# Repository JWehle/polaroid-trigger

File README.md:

# polaroid-trigger
Automated trigger board for a polaroid SX-70 type camera.

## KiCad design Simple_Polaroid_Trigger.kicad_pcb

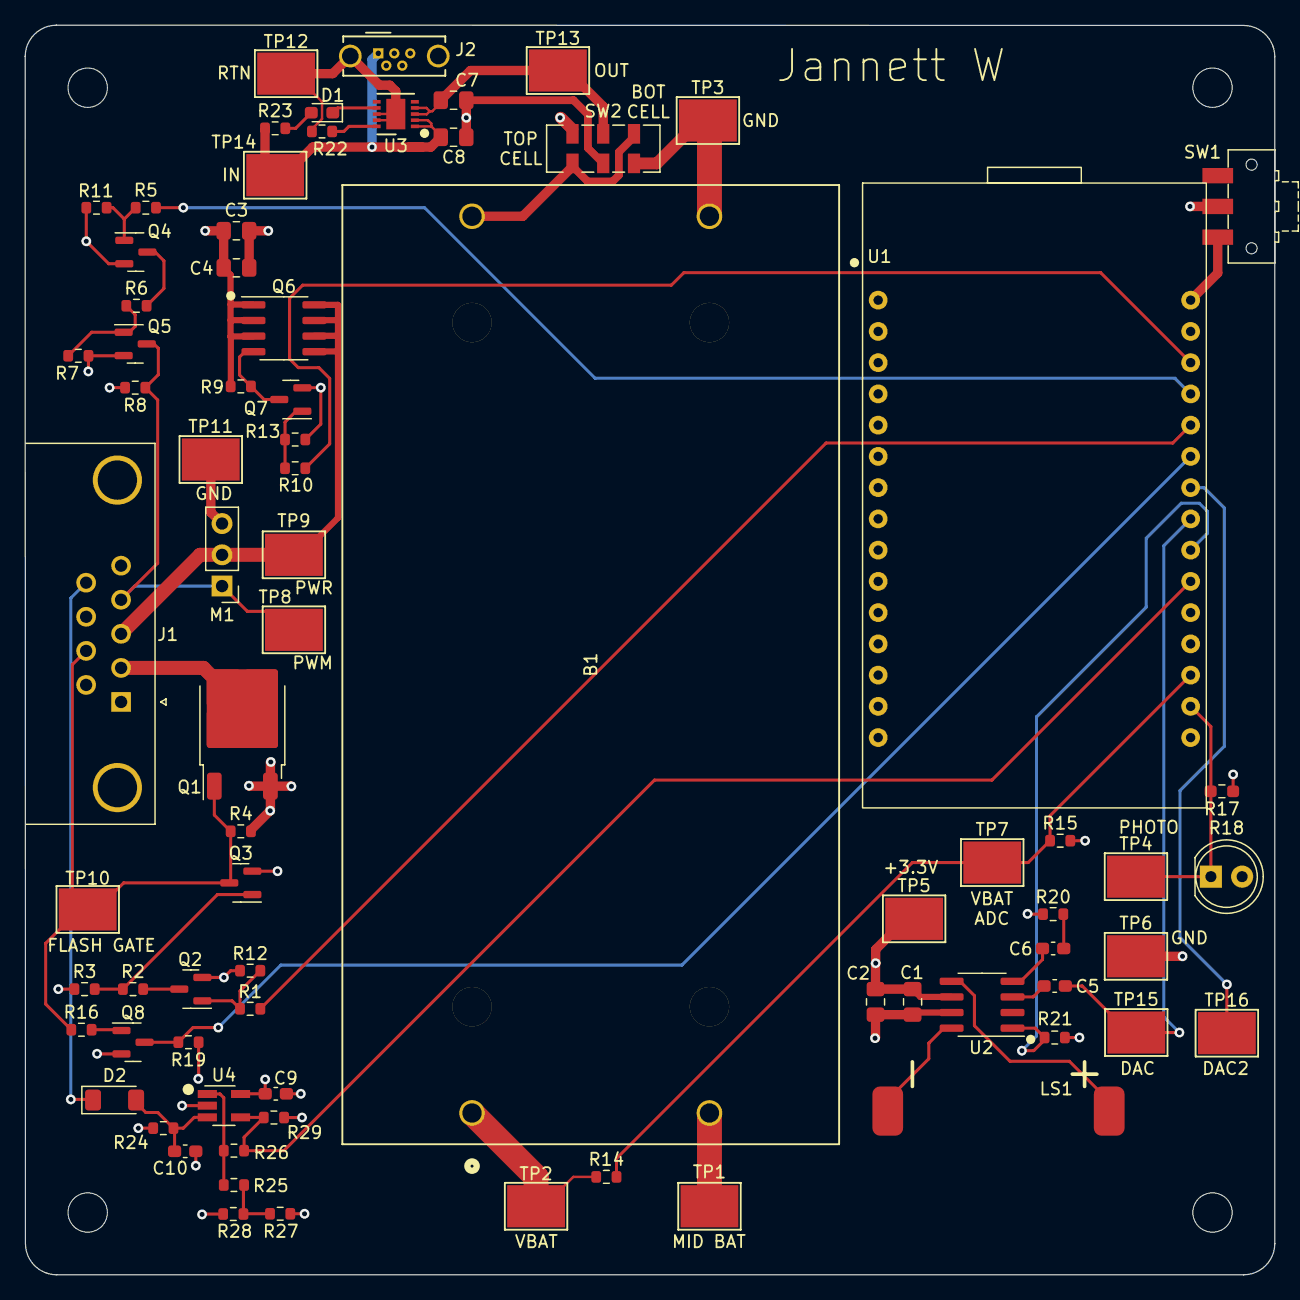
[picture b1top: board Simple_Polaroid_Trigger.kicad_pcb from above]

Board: 4 copper layers, 101.6 x 101.6 mm, 80 parts (0 on the bottom side), 43 nets.

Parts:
B1: BK-18650-PC4; BK-18650-PC4_MPD
C1, C3, C7, C8: 10uF; C_0805_2012Metric_Pad1.18x1.45mm_HandSolder
C2, C4: 1uF; C_0805_2012Metric_Pad1.18x1.45mm_HandSolder
C5, C6, C9, C10: 0.1uF; C_0603_1608Metric_Pad1.08x0.95mm_HandSolder
D1: LED; LED_0603_1608Metric_Pad1.05x0.95mm_HandSolder
D2: BAV103-GS08; D_MiniMELF
H1, H2, H3, H4: MountingHole; MountingHole_3.2mm_M3
J1: DE9_Receptacle_MountingHoles; DSUB-9_Female_Horizontal_P2.77x2.84mm_EdgePinOffset4.94mm_H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
J2: 614105150721; USB_Micro-B_Wuerth_614105150721_Vertical_CircularHoles
LS1: OWS-142037TA-4
M1: Motor_Servo; PinHeader_1x03_P2.54mm_Vertical
Q1: QM6006D; TO-252-2
Q2, Q4, Q7, Q8: MMBT3904; SOT-23
Q3, Q5: MMBT3906; SOT-23
Q6: FDS9435A; SOIC-8_3.9x4.9mm_P1.27mm
R1, R2, R5, R6, R9, R10, R15, R16, R19, R21, R22, R24, R25, R27, R28, R29: 10K; R_0603_1608Metric
R3, R4, R7, R8, R11, R12, R13, R23: 1K; R_0603_1608Metric
R14: 20K; R_0603_1608Metric
R17: 10K; R_0603_1608Metric_Pad0.98x0.95mm_HandSolder
R18: R_Photo; LED_D5.0mm
R20: 0; R_0603_1608Metric
R26: 1Meg; R_0603_1608Metric
SW1: JS102011SAQN; SW_SPDT_CK-JS102011SAQN
SW2: JS202011JCQN; SW_DPDT_CK_JS202011JCQN
TP1, TP2, TP3, TP4, TP5, TP6, TP7, TP8, TP9, TP10, TP11, TP12, TP13, TP14, TP15, TP16: 5016; TestPoint_Keystone_5016_Compact
U1: ESP32_MODULE
U2: PAM8302AAD; SOIC-8_3.9x4.9mm_P1.27mm
U3: MCP73123T-22SI/MF; DFN-10-1EP_3x3mm_P0.5mm_EP1.55x2.48mm
U4: TLV1701AIDBVT; SOT-23-5_HandSoldering

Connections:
+3.3V: C1.1, C2.1, C9.2, R17.1, R19.1, R24.1, R28.1, R29.1, TP5.1, U1.1 (+3.3V), U2.6 (VDD), U4.5 (V+)
/BAT_MID: B1.2, B1.4, SW2.3 (C), SW2.4 (A), TP1.1
/BW_IN: D2.1 (K), J1.9
/CHARGER_IN: C8.1, J2.1 (VBUS), R23.1, TP14.1, U3.1 (VDD), U3.2 (VDD)
/CHARGER_OUT: C7.1, SW2.2 (B), TP13.1, U3.3 (VBAT), U3.4 (VBAT)
/CHARGER_RTN: C7.2, C8.2, J2.5 (GND), J2.6 (Shield), R22.2, SW2.5 (B), TP12.1, U3.8 (VSS), U3.9 (VSS), U3.11 (EP)
/ESP_PWR: SW1.1 (A), U1.30 (VIN)
/FLASH_GATE: J1.7, Q1.1 (G), Q3.3 (C), R4.1, R16.1, TP10.1
/FLASH_OUT: J1.2, Q1.2 (D)
/PHOTORES: R17.2, R18.1, TP4.1, U1.17 (GPIO36)
/SERVO_PWM_H: J1.4, M1.1 (PWM), Q5.3 (C), R8.1, TP8.1
/SERVO_PWR: J1.3, M1.2 (+), Q6.5 (D), Q6.6 (D), Q6.7 (D), Q6.8 (D), TP9.1
/VBAT_ADC: R14.2, R15.1, TP7.1, U1.18 (GPIO39)
BW_INT: R26.1, R29.2, U1.21 (GPIO32), U4.4
DAC: C5.1, TP15.1, U1.23 (GPIO25)
EN_AUDIO: R21.1, U1.22 (GPIO33), U2.1 (~SD)
FLASH: R1.2, U1.26 (GPIO14)
FLASH_FB: Q8.3 (C), R19.2, U1.25 (GPIO27)
GND: B1.3, C1.2, C2.2, C3.2, C4.2, C9.1, C10.2, J1.0 (PAD), J1.5, J1.8, M1.3 (-), Q1.3 (S), Q2.2 (E), Q4.2 (E), Q7.2 (E), Q8.2 (E), R4.2, R8.2, R11.2, R12.2, R13.2, R15.2, R18.2, R20.2, R21.2, R27.2, SW2.6 (C), TP3.1, TP6.1, TP11.1, U1.2 (GND), U1.29 (GND), U2.7 (GND), U4.2 (V-)
unnamed: C6.1, R20.1
unnamed: D1.2 (A), R23.2
unnamed: D1.1 (K), U3.7 (STAT)
unnamed: C10.1, D2.2 (A), R24.2, U4.3 (-)
unnamed: Q2.1 (B), R1.1, R12.1
unnamed: Q2.3 (C), R2.2
unnamed: Q3.1 (B), R2.1, R3.2
unnamed: Q4.1 (B), R5.1, R11.1
unnamed: Q4.3 (C), R6.2
unnamed: Q5.1 (B), R6.1, R7.2
unnamed: Q6.4 (G), Q7.3 (C), R9.2
unnamed: Q7.1 (B), R10.1, R13.1
unnamed: Q8.1 (B), R16.2
unnamed: R25.2, R27.1, R28.2
unnamed: TP16.1, U1.24 (GPIO26)
unnamed: C5.2, U2.3 (IN+)
unnamed: C6.2, U2.4 (IN-)
unnamed: LS1.1, U2.5 (OUT+)
unnamed: LS1.2, U2.8 (OUT-)
unnamed: R22.1, U3.10 (PROG)
unnamed: R25.1, R26.2, U4.1 (+)
SERVO_GATE: R10.2, U1.28 (GPIO13)
SERVO_PWM: R5.2, U1.27 (GPIO12)
VBAT: B1.1, C3.1, C4.1, J1.1, J1.6, Q3.2 (E), Q5.2 (E), Q6.1 (S), Q6.2 (S), Q6.3 (S), R3.1, R7.1, R9.1, R14.1, SW1.2 (B), SW2.1 (A), TP2.1
